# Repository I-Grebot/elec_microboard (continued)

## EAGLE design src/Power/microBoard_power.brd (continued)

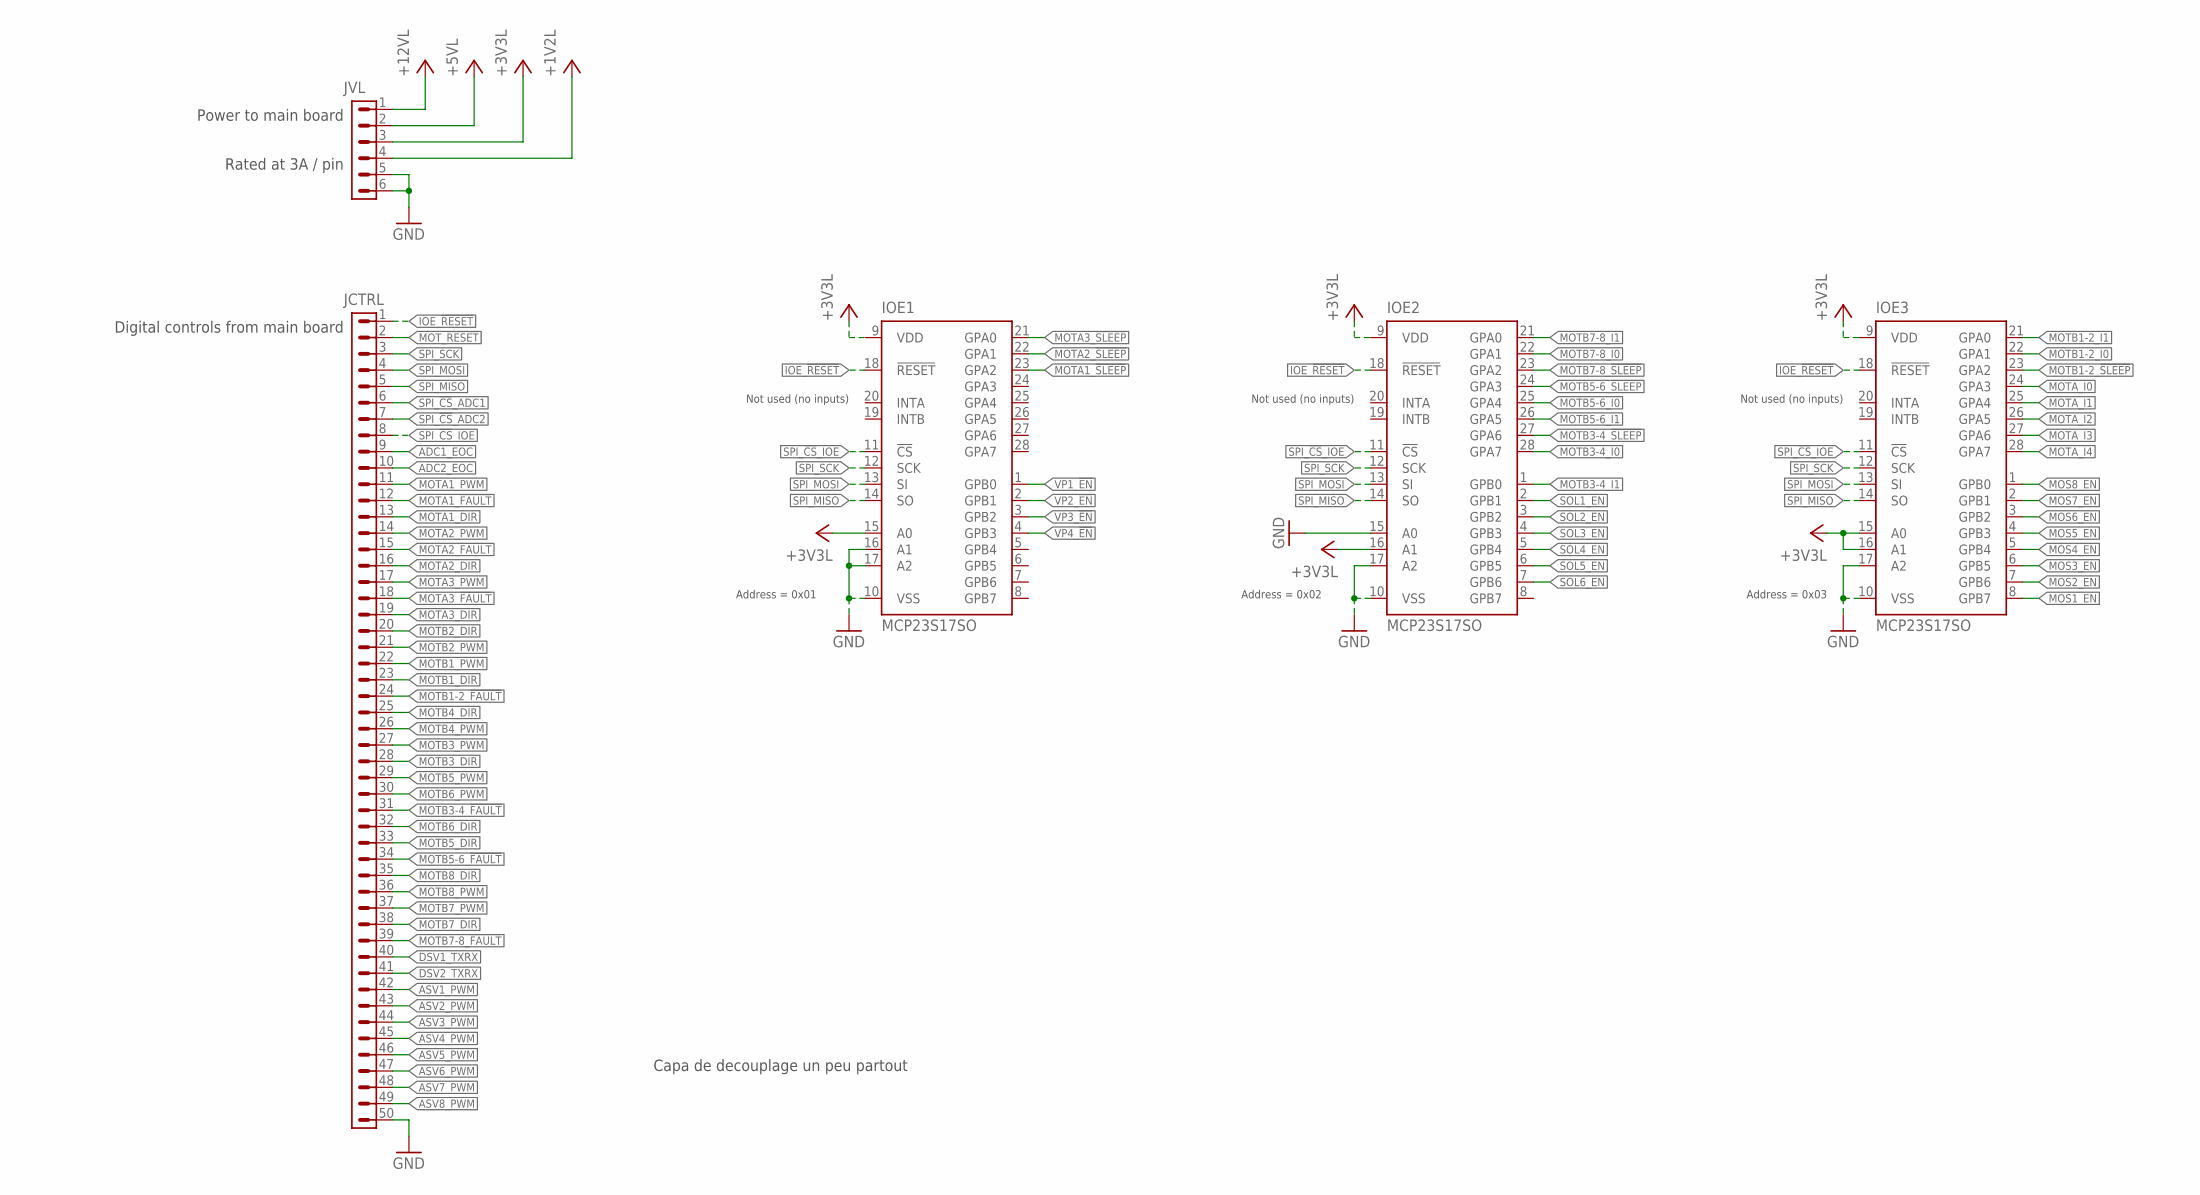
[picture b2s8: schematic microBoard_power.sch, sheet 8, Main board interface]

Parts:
IOE1, IOE2, IOE3: MCP23S17SO; SO28W
JCTRL: FFC-0.5_50; FFC-SMD-0.5_50
JVL: HE14_H_6

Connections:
+1V2L: JVL.4; also elsewhere on the board
+3V3L: IOE1.9 (VDD), IOE1.15 (A0), IOE2.9 (VDD), IOE2.16 (A1), IOE3.9 (VDD), IOE3.15 (A0), IOE3.16 (A1), JVL.3; also elsewhere on the board
+5VL: JVL.2; also elsewhere on the board
+12VL: JVL.1; also elsewhere on the board
ADC1_EOC: JCTRL.9; also elsewhere on the board
ADC2_EOC: JCTRL.10; also elsewhere on the board
ASV1_PWM: JCTRL.42; also elsewhere on the board
ASV2_PWM: JCTRL.43; also elsewhere on the board
ASV3_PWM: JCTRL.44; also elsewhere on the board
ASV4_PWM: JCTRL.45; also elsewhere on the board
ASV5_PWM: JCTRL.46; also elsewhere on the board
ASV6_PWM: JCTRL.47; also elsewhere on the board
ASV7_PWM: JCTRL.48; also elsewhere on the board
ASV8_PWM: JCTRL.49; also elsewhere on the board
DSV1_TXRX: JCTRL.40; also elsewhere on the board
DSV2_TXRX: JCTRL.41
GND: IOE1.10 (VSS), IOE1.16 (A1), IOE1.17 (A2), IOE2.10 (VSS), IOE2.15 (A0), IOE2.17 (A2), IOE3.10 (VSS), IOE3.17 (A2), JCTRL.50, JVL.5, JVL.6; also elsewhere on the board
IOE_!RESET!: IOE1.18 (!RESET), IOE2.18 (!RESET), IOE3.18 (!RESET), JCTRL.1
MOS1_EN: IOE3.8 (GPB7); also elsewhere on the board
MOS2_EN: IOE3.7 (GPB6); also elsewhere on the board
MOS3_EN: IOE3.6 (GPB5); also elsewhere on the board
MOS4_EN: IOE3.5 (GPB4); also elsewhere on the board
MOS5_EN: IOE3.4 (GPB3); also elsewhere on the board
MOS6_EN: IOE3.3 (GPB2); also elsewhere on the board
MOS7_EN: IOE3.2 (GPB1); also elsewhere on the board
MOS8_EN: IOE3.1 (GPB0); also elsewhere on the board
MOTA1_!FAULT!: JCTRL.12; also elsewhere on the board
MOTA1_!SLEEP!: IOE1.23 (GPA2); also elsewhere on the board
MOTA1_DIR: JCTRL.13; also elsewhere on the board
MOTA1_PWM: JCTRL.11; also elsewhere on the board
MOTA2_!FAULT!: JCTRL.15; also elsewhere on the board
MOTA2_!SLEEP!: IOE1.22 (GPA1); also elsewhere on the board
MOTA2_DIR: JCTRL.16; also elsewhere on the board
MOTA2_PWM: JCTRL.14; also elsewhere on the board
MOTA3_!FAULT!: JCTRL.18; also elsewhere on the board
MOTA3_!SLEEP!: IOE1.21 (GPA0); also elsewhere on the board
MOTA3_DIR: JCTRL.19; also elsewhere on the board
MOTA3_PWM: JCTRL.17; also elsewhere on the board
MOTA_I0: IOE3.24 (GPA3); also elsewhere on the board
MOTA_I1: IOE3.25 (GPA4); also elsewhere on the board
MOTA_I2: IOE3.26 (GPA5); also elsewhere on the board
MOTA_I3: IOE3.27 (GPA6); also elsewhere on the board
MOTA_I4: IOE3.28 (GPA7); also elsewhere on the board
MOTB1-2_!FAULT!: JCTRL.24; also elsewhere on the board
MOTB1-2_!SLEEP!: IOE3.23 (GPA2); also elsewhere on the board
MOTB1-2_I0: IOE3.22 (GPA1); also elsewhere on the board
MOTB1-2_I1: IOE3.21 (GPA0); also elsewhere on the board
MOTB1_DIR: JCTRL.23; also elsewhere on the board
MOTB1_PWM: JCTRL.22; also elsewhere on the board
MOTB2_DIR: JCTRL.20; also elsewhere on the board
MOTB2_PWM: JCTRL.21; also elsewhere on the board
MOTB3-4_!FAULT!: JCTRL.31; also elsewhere on the board
MOTB3-4_!SLEEP!: IOE2.27 (GPA6); also elsewhere on the board
MOTB3-4_I0: IOE2.28 (GPA7); also elsewhere on the board
MOTB3-4_I1: IOE2.1 (GPB0); also elsewhere on the board
MOTB3_DIR: JCTRL.28; also elsewhere on the board
MOTB3_PWM: JCTRL.27; also elsewhere on the board
MOTB4_DIR: JCTRL.25; also elsewhere on the board
MOTB4_PWM: JCTRL.26; also elsewhere on the board
MOTB5-6_!FAULT!: JCTRL.34; also elsewhere on the board
MOTB5-6_!SLEEP!: IOE2.24 (GPA3); also elsewhere on the board
MOTB5-6_I0: IOE2.25 (GPA4); also elsewhere on the board
MOTB5-6_I1: IOE2.26 (GPA5); also elsewhere on the board
MOTB5_DIR: JCTRL.33; also elsewhere on the board
MOTB5_PWM: JCTRL.29; also elsewhere on the board
MOTB6_DIR: JCTRL.32; also elsewhere on the board
MOTB6_PWM: JCTRL.30; also elsewhere on the board
MOTB7-8_!FAULT!: JCTRL.39; also elsewhere on the board
MOTB7-8_!SLEEP!: IOE2.23 (GPA2); also elsewhere on the board
MOTB7-8_I0: IOE2.22 (GPA1); also elsewhere on the board
MOTB7-8_I1: IOE2.21 (GPA0); also elsewhere on the board
MOTB7_DIR: JCTRL.38; also elsewhere on the board
MOTB7_PWM: JCTRL.37; also elsewhere on the board
MOTB8_DIR: JCTRL.35; also elsewhere on the board
MOTB8_PWM: JCTRL.36; also elsewhere on the board
MOT_!RESET!: JCTRL.2; also elsewhere on the board
SOL1_EN: IOE2.2 (GPB1); also elsewhere on the board
SOL2_EN: IOE2.3 (GPB2); also elsewhere on the board
SOL3_EN: IOE2.4 (GPB3); also elsewhere on the board
SOL4_EN: IOE2.5 (GPB4); also elsewhere on the board
SOL5_EN: IOE2.6 (GPB5); also elsewhere on the board
SOL6_EN: IOE2.7 (GPB6); also elsewhere on the board
SPI_!CS!_ADC1: JCTRL.6; also elsewhere on the board
SPI_!CS!_ADC2: JCTRL.7; also elsewhere on the board
SPI_!CS!_IOE: IOE1.11 (!CS), IOE2.11 (!CS), IOE3.11 (!CS), JCTRL.8
SPI_MISO: IOE1.14 (SO), IOE2.14 (SO), IOE3.14 (SO), JCTRL.5; also elsewhere on the board
SPI_MOSI: IOE1.13 (SI), IOE2.13 (SI), IOE3.13 (SI), JCTRL.4; also elsewhere on the board
SPI_SCK: IOE1.12 (SCK), IOE2.12 (SCK), IOE3.12 (SCK), JCTRL.3; also elsewhere on the board
VP1_!EN!: IOE1.1 (GPB0); also elsewhere on the board
VP2_!EN!: IOE1.2 (GPB1); also elsewhere on the board
VP3_!EN!: IOE1.3 (GPB2); also elsewhere on the board
VP4_!EN!: IOE1.4 (GPB3); also elsewhere on the board

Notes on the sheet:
Not used (no inputs)
Power to main board
Rated at 3A / pin
Digital controls from main board
Address = 0x01
Address = 0x02
Address = 0x03
Capa de decouplage un peu partout

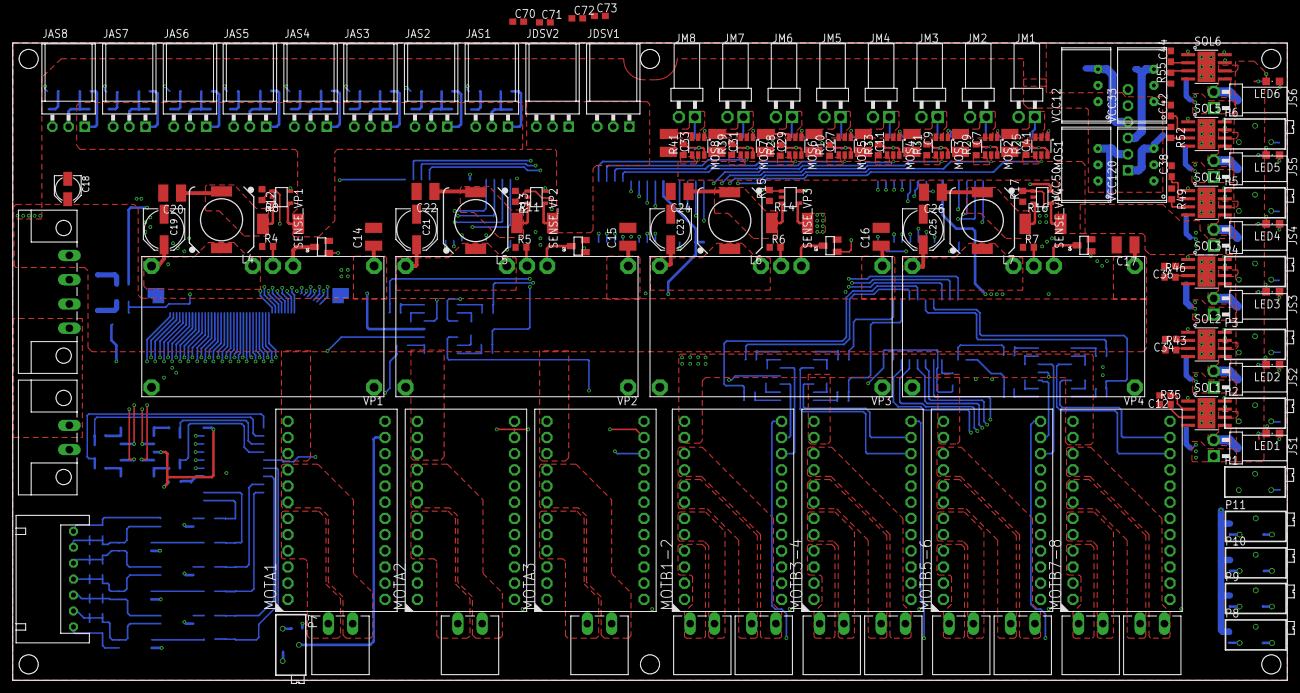
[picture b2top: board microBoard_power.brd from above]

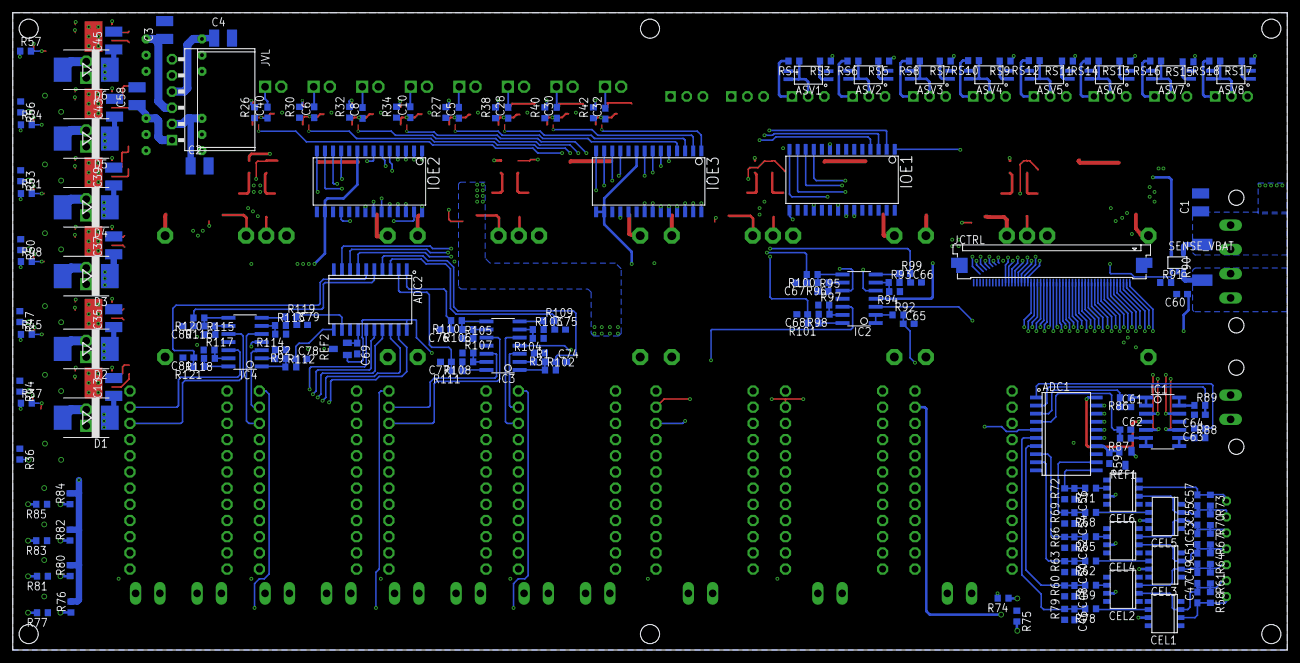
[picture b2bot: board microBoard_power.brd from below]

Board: 4 copper layers, 200.0 x 100.0 mm, 341 parts (188 on the bottom side), 314 nets.

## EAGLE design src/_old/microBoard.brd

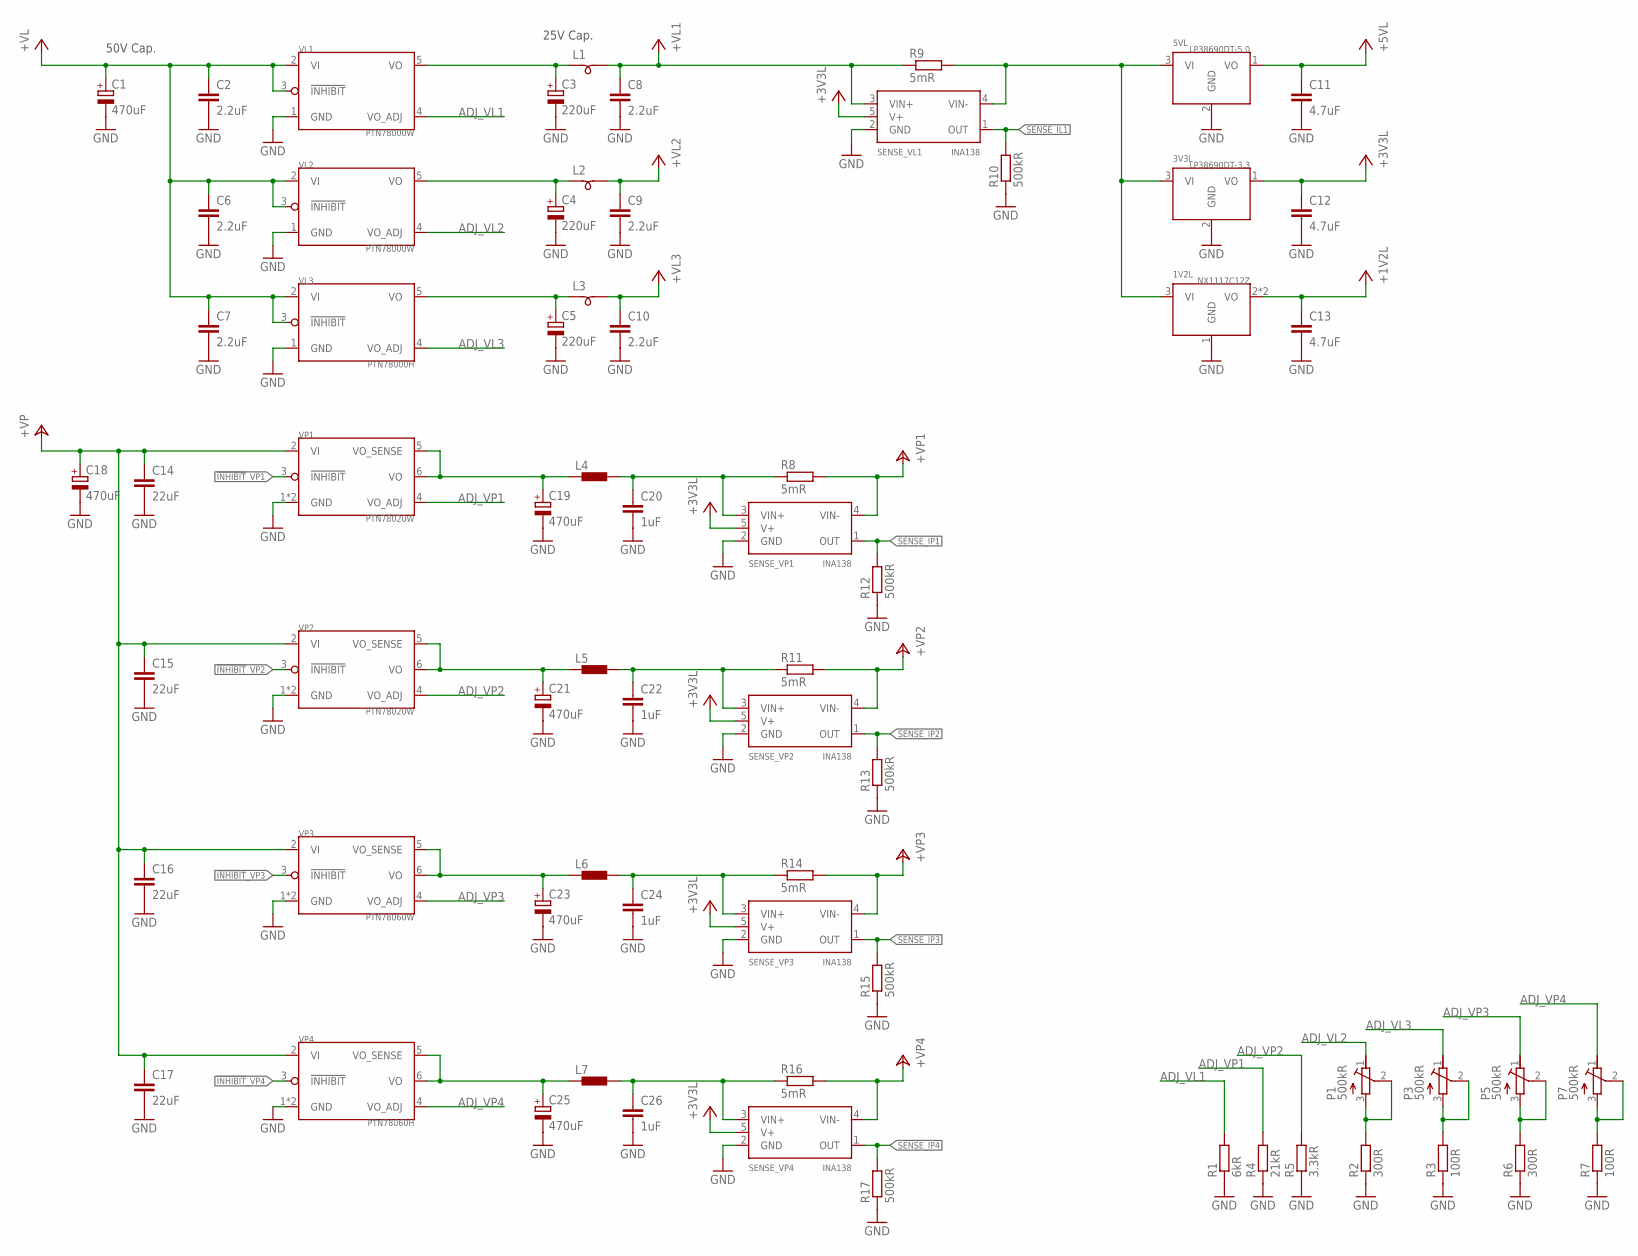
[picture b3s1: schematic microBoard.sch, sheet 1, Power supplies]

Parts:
1V2L: NX1117C12Z; SOT_223
3V3L: LP38690DT-3.3; NDP_0003B
5VL: LP38690DT-5.0; NDP_0003B
C1, C18: 470uF; PANASONIC_B
C2, C6, C7, C8, C9, C10: 2.2uF; C3225
C3, C4, C5: 220uF; PANASONIC_B
C11, C12, C13: 4.7uF; C3225
C14, C15, C16, C17: 22uF; C3225
C19, C21, C23, C25: 470uF; PANASONIC_D
C20, C22, C24, C26: 1uF; C3225
L1, L2, L3: SM-B9
L4, L5, L6, L7: DR1030
P1, P3, P5, P7: 500kR; RTRIMT93XB
R1: 6kR; R0603
R2, R6: 300R; R0603
R3, R7: 100R; R0603
R4: 21kR; R0603
R5: 3.3kR; R0603
R8, R9, R11, R14, R16: 5mR; R2512
R10, R12, R13, R15, R17: 500kR; R0603
SENSE_VL1: INA138; DBV_05
SENSE_VP1, SENSE_VP2, SENSE_VP3, SENSE_VP4: INA138; DBV_05
VL1, VL2: PTN78000W; PTN78000
VL3: PTN78000H; PTN78000
VP1, VP2: PTN78020W; PTN78020
VP3: PTN78060W; PTN78060
VP4: PTN78060H; PTN78060

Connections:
!INHIBIT!_VP1: VP1.3 (!INHIBIT!)
!INHIBIT!_VP2: VP2.3 (!INHIBIT!)
!INHIBIT!_VP3: VP3.3 (!INHIBIT!)
!INHIBIT!_VP4: VP4.3 (!INHIBIT!)
+1V2L: 1V2L.2 (VO), 1V2L.4 (VO), C13.1; also elsewhere on the board
+3V3L: 3V3L.1 (VO), C12.1, SENSE_VL1.5 (V+), SENSE_VP1.5 (V+), SENSE_VP2.5 (V+), SENSE_VP3.5 (V+), SENSE_VP4.5 (V+); also elsewhere on the board
+5VL: 5VL.1 (VO), C11.1; also elsewhere on the board
+VL: C1.+, C2.1, C6.1, C7.1, VL1.2 (VI), VL1.3 (!INHIBIT!), VL2.2 (VI), VL2.3 (!INHIBIT!), VL3.2 (VI), VL3.3 (!INHIBIT!)
+VL1: C8.1, L1.2, R9.1, SENSE_VL1.3 (VIN+)
+VL2: C9.1, L2.2; also elsewhere on the board
+VL3: C10.1, L3.2
+VP: C14.1, C15.1, C16.1, C17.1, C18.+, VP1.2 (VI), VP2.2 (VI), VP3.2 (VI), VP4.2 (VI); also elsewhere on the board
+VP1: R8.2, SENSE_VP1.4 (VIN-); also elsewhere on the board
+VP2: R11.2, SENSE_VP2.4 (VIN-)
+VP3: R14.2, SENSE_VP3.4 (VIN-); also elsewhere on the board
+VP4: R16.2, SENSE_VP4.4 (VIN-); also elsewhere on the board
ADJ_VL1: R1.2, VL1.4 (VO_ADJ)
ADJ_VL2: P1.1 (A), VL2.4 (VO_ADJ)
ADJ_VL3: P3.1 (A), VL3.4 (VO_ADJ)
ADJ_VP1: R4.2, VP1.4 (VO_ADJ)
ADJ_VP2: R5.2, VP2.4 (VO_ADJ)
ADJ_VP3: P5.1 (A), VP3.4 (VO_ADJ)
ADJ_VP4: P7.1 (A), VP4.4 (VO_ADJ)
GND: 1V2L.1 (GND), 3V3L.2 (GND), 5VL.2 (GND), C1.-, C2.2, C3.-, C4.-, C5.-, C6.2, C7.2, C8.2, C9.2, C10.2, C11.2, C12.2, C13.2, C14.2, C15.2, C16.2, C17.2, C18.-, C19.-, C20.2, C21.-, C22.2, C23.-, C24.2, C25.-, C26.2, R1.1, R2.1, R3.1, R4.1, R5.1, R6.1, R7.1, R10.1, R12.1, R13.1, R15.1, R17.1, SENSE_VL1.2 (GND), SENSE_VP1.2 (GND), SENSE_VP2.2 (GND), SENSE_VP3.2 (GND), SENSE_VP4.2 (GND), VL1.1 (GND), VL2.1 (GND), VL3.1 (GND), VP1.1 (GND), VP1.7 (GND), VP2.1 (GND), VP2.7 (GND), VP3.1 (GND), VP3.7 (GND), VP4.1 (GND), VP4.7 (GND); also elsewhere on the board
unnamed: C19.+, L4.1, VP1.5 (VO_SENSE), VP1.6 (VO)
unnamed: P1.2 (S), P1.3 (E), R2.2
unnamed: C20.1, L4.2, R8.1, SENSE_VP1.3 (VIN+)
unnamed: P3.2 (S), P3.3 (E), R3.2
unnamed: P5.2 (S), P5.3 (E), R6.2
unnamed: C21.+, L5.1, VP2.5 (VO_SENSE), VP2.6 (VO)
unnamed: C3.+, L1.1, VL1.5 (VO)
unnamed: C4.+, L2.1, VL2.5 (VO)
unnamed: C5.+, L3.1, VL3.5 (VO)
unnamed: P7.2 (S), P7.3 (E), R7.2
unnamed: C22.1, L5.2, R11.1, SENSE_VP2.3 (VIN+)
unnamed: C23.+, L6.1, VP3.5 (VO_SENSE), VP3.6 (VO)
unnamed: C24.1, L6.2, R14.1, SENSE_VP3.3 (VIN+)
unnamed: C25.+, L7.1, VP4.5 (VO_SENSE), VP4.6 (VO)
unnamed: C26.1, L7.2, R16.1, SENSE_VP4.3 (VIN+)
SENSE_IL1: R10.2, SENSE_VL1.1 (OUT); also elsewhere on the board
SENSE_IP1: R12.2, SENSE_VP1.1 (OUT); also elsewhere on the board
SENSE_IP2: R13.2, SENSE_VP2.1 (OUT); also elsewhere on the board
SENSE_IP3: R15.2, SENSE_VP3.1 (OUT); also elsewhere on the board
SENSE_IP4: R17.2, SENSE_VP4.1 (OUT); also elsewhere on the board
VS1: 1V2L.3 (VI), 3V3L.3 (VI), 5VL.3 (VI), R9.2, SENSE_VL1.4 (VIN-)

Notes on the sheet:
50V Cap.
25V Cap.

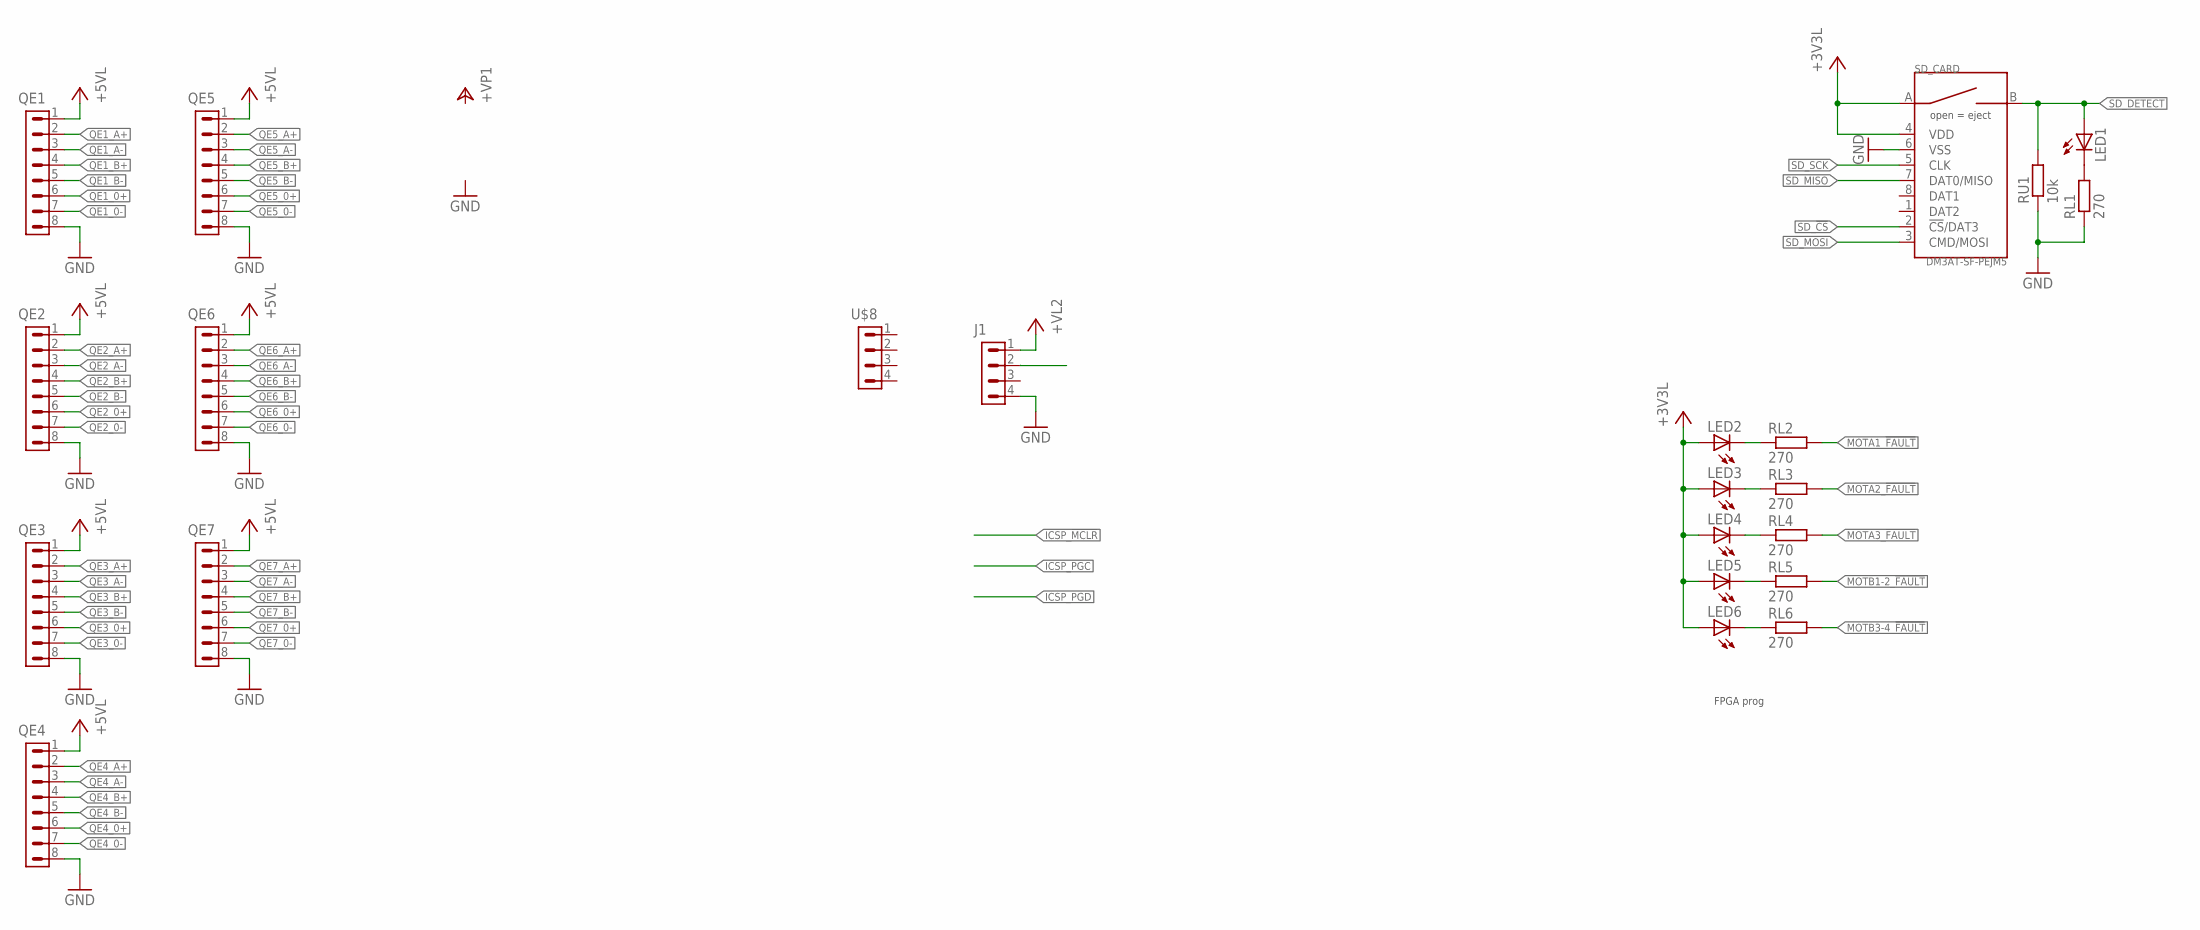
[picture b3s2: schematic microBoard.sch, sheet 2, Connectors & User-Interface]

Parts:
J1: CON_1.27_4
LED1, LED2, LED3, LED4, LED5, LED6: LEDCHIP-LED0805; CHIP-LED0805
QE1, QE2, QE3, QE4, QE5, QE6, QE7: CON_1.27_8
RL1, RL2, RL3, RL4, RL5, RL6: 270; R0603
RU1: 10k; R0603
SD_CARD: DM3AT-SF-PEJM5; DM3AT
U$8: CON_1.25_4

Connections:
+3V3L: LED2.A, LED3.A, LED4.A, LED5.A, LED6.A, SD_CARD.4 (VDD), SD_CARD.A; also elsewhere on the board
+5VL: QE1.1, QE2.1, QE3.1, QE4.1, QE5.1, QE6.1, QE7.1; also elsewhere on the board
+VL2: J1.1; also elsewhere on the board
GND: J1.4, QE1.8, QE2.8, QE3.8, QE4.8, QE5.8, QE6.8, QE7.8, RL1.1, RU1.1, SD_CARD.6 (VSS); also elsewhere on the board
MOTA1_!FAULT!: RL2.2; also elsewhere on the board
MOTA2_!FAULT!: RL3.2; also elsewhere on the board
MOTA3_!FAULT!: RL4.2; also elsewhere on the board
MOTB1-2_!FAULT!: RL5.2; also elsewhere on the board
MOTB3-4_!FAULT!: RL6.2; also elsewhere on the board
unnamed: LED1.C, RL1.2
unnamed: LED2.C, RL2.1
unnamed: LED3.C, RL3.1
unnamed: LED4.C, RL4.1
unnamed: LED5.C, RL5.1
unnamed: LED6.C, RL6.1
QE1_0+: QE1.6; also elsewhere on the board
QE1_0-: QE1.7; also elsewhere on the board
QE1_A+: QE1.2; also elsewhere on the board
QE1_A-: QE1.3; also elsewhere on the board
QE1_B+: QE1.4; also elsewhere on the board
QE1_B-: QE1.5; also elsewhere on the board
QE2_0+: QE2.6; also elsewhere on the board
QE2_0-: QE2.7; also elsewhere on the board
QE2_A+: QE2.2; also elsewhere on the board
QE2_A-: QE2.3; also elsewhere on the board
QE2_B+: QE2.4; also elsewhere on the board
QE2_B-: QE2.5; also elsewhere on the board
QE3_0+: QE3.6; also elsewhere on the board
QE3_0-: QE3.7; also elsewhere on the board
QE3_A+: QE3.2; also elsewhere on the board
QE3_A-: QE3.3; also elsewhere on the board
QE3_B+: QE3.4; also elsewhere on the board
QE3_B-: QE3.5; also elsewhere on the board
QE4_0+: QE4.6; also elsewhere on the board
QE4_0-: QE4.7; also elsewhere on the board
QE4_A+: QE4.2; also elsewhere on the board
QE4_A-: QE4.3; also elsewhere on the board
QE4_B+: QE4.4; also elsewhere on the board
QE4_B-: QE4.5; also elsewhere on the board
QE5_0+: QE5.6; also elsewhere on the board
QE5_0-: QE5.7; also elsewhere on the board
QE5_A+: QE5.2; also elsewhere on the board
QE5_A-: QE5.3; also elsewhere on the board
QE5_B+: QE5.4; also elsewhere on the board
QE5_B-: QE5.5; also elsewhere on the board
QE6_0+: QE6.6; also elsewhere on the board
QE6_0-: QE6.7; also elsewhere on the board
QE6_A+: QE6.2; also elsewhere on the board
QE6_A-: QE6.3; also elsewhere on the board
QE6_B+: QE6.4; also elsewhere on the board
QE6_B-: QE6.5; also elsewhere on the board
QE7_0+: QE7.6; also elsewhere on the board
QE7_0-: QE7.7; also elsewhere on the board
QE7_A+: QE7.2; also elsewhere on the board
QE7_A-: QE7.3; also elsewhere on the board
QE7_B+: QE7.4; also elsewhere on the board
QE7_B-: QE7.5; also elsewhere on the board
SD_!CS!: SD_CARD.2 (!CS!/DAT3); also elsewhere on the board
SD_DETECT: LED1.A, RU1.2, SD_CARD.B
SD_MISO: SD_CARD.7 (DAT0/MISO); also elsewhere on the board
SD_MOSI: SD_CARD.3 (CMD/MOSI); also elsewhere on the board
SD_SCK: SD_CARD.5 (CLK); also elsewhere on the board

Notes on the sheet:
FPGA prog

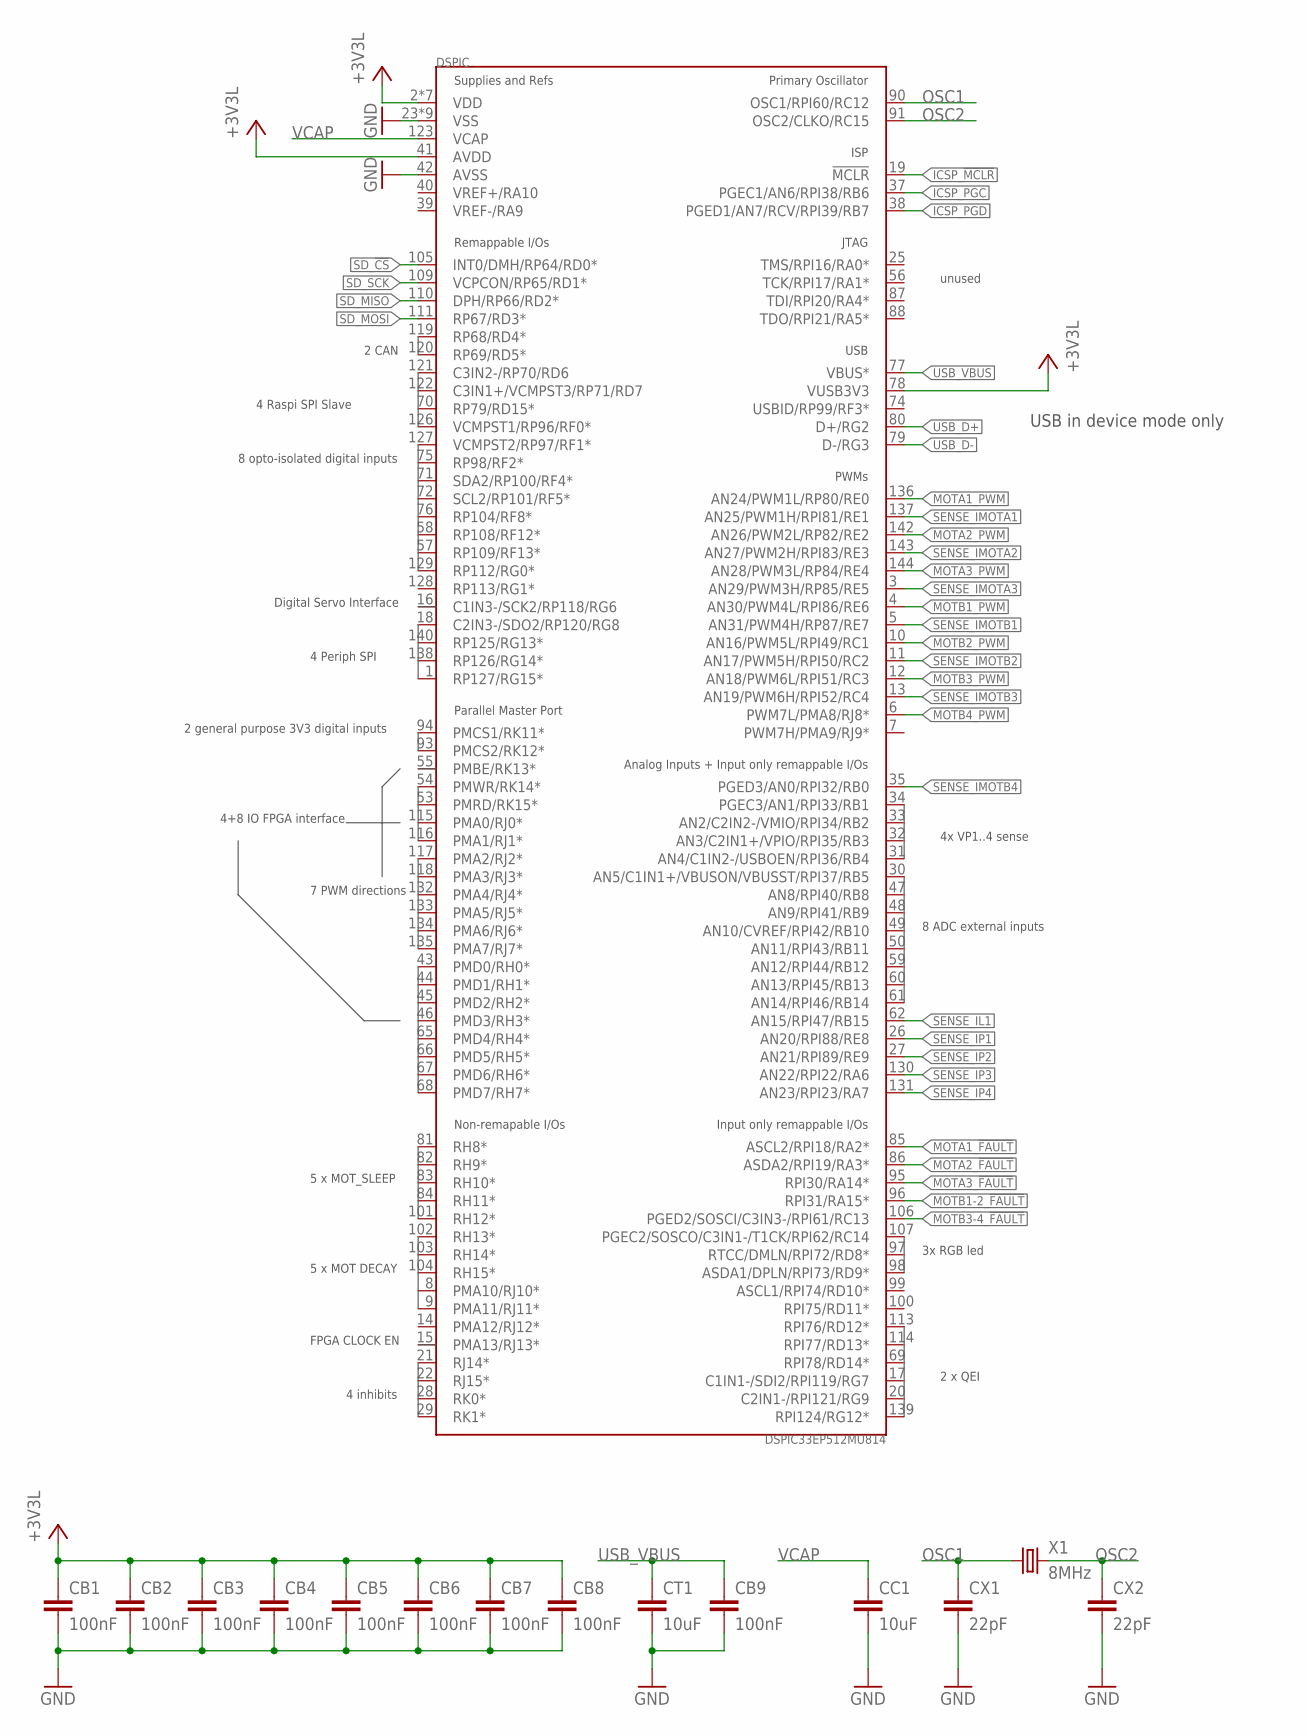
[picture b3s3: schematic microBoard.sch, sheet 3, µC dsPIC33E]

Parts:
CB1, CB2, CB3, CB4, CB5, CB6, CB7, CB8, CB9: 100nF; C0603
CC1: 10uF; C1210
CT1: 10uF; C1210
CX1, CX2: 22pF; C0603
DSPIC: DSPIC33EP512MU814; TQFP_144
X1: 8MHz; CTS406

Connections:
+3V3L: CB1.1, CB2.1, CB3.1, CB4.1, CB5.1, CB6.1, CB7.1, CB8.1, DSPIC.2 (VDD), DSPIC.24 (VDD), DSPIC.41 (AVDD), DSPIC.52 (VDD), DSPIC.64 (VDD), DSPIC.78 (VUSB3V3), DSPIC.89 (VDD), DSPIC.112 (VDD), DSPIC.124 (VDD); also elsewhere on the board
GND: CB1.2, CB2.2, CB3.2, CB4.2, CB5.2, CB6.2, CB7.2, CB8.2, CB9.2, CC1.2, CT1.2, CX1.2, CX2.2, DSPIC.23 (VSS), DSPIC.36 (VSS), DSPIC.42 (AVSS), DSPIC.51 (VSS), DSPIC.63 (VSS), DSPIC.73 (VSS), DSPIC.92 (VSS), DSPIC.108 (VSS), DSPIC.125 (VSS), DSPIC.141 (VSS); also elsewhere on the board
ICSP_!MCLR!: DSPIC.19 (!MCLR!)
ICSP_PGC: DSPIC.37 (PGEC1/AN6/RPI38/RB6)
ICSP_PGD: DSPIC.38 (PGED1/AN7/RCV/RPI39/RB7)
MOTA1_!FAULT!: DSPIC.85 (ASCL2/RPI18/RA2*); also elsewhere on the board
MOTA1_PWM: DSPIC.136 (AN24/PWM1L/RP80/RE0); also elsewhere on the board
MOTA2_!FAULT!: DSPIC.86 (ASDA2/RPI19/RA3*); also elsewhere on the board
MOTA2_PWM: DSPIC.142 (AN26/PWM2L/RP82/RE2); also elsewhere on the board
MOTA3_!FAULT!: DSPIC.95 (RPI30/RA14*); also elsewhere on the board
MOTA3_PWM: DSPIC.144 (AN28/PWM3L/RP84/RE4); also elsewhere on the board
MOTB1-2_!FAULT!: DSPIC.96 (RPI31/RA15*); also elsewhere on the board
MOTB1_PWM: DSPIC.4 (AN30/PWM4L/RPI86/RE6); also elsewhere on the board
MOTB2_PWM: DSPIC.10 (AN16/PWM5L/RPI49/RC1); also elsewhere on the board
MOTB3-4_!FAULT!: DSPIC.106 (PGED2/SOSCI/C3IN3-/RPI61/RC13); also elsewhere on the board
MOTB3_PWM: DSPIC.12 (AN18/PWM6L/RPI51/RC3); also elsewhere on the board
MOTB4_PWM: DSPIC.6 (PWM7L/PMA8/RJ8*); also elsewhere on the board
OSC1: CX1.1, DSPIC.90 (OSC1/RPI60/RC12), X1.1
OSC2: CX2.1, DSPIC.91 (OSC2/CLKO/RC15), X1.3 (2)
SD_!CS!: DSPIC.105 (INT0/DMH/RP64/RD0*); also elsewhere on the board
SD_MISO: DSPIC.110 (DPH/RP66/RD2*); also elsewhere on the board
SD_MOSI: DSPIC.111 (RP67/RD3*); also elsewhere on the board
SD_SCK: DSPIC.109 (VCPCON/RP65/RD1*); also elsewhere on the board
SENSE_IL1: DSPIC.62 (AN15/RPI47/RB15); also elsewhere on the board
SENSE_IMOTA1: DSPIC.137 (AN25/PWM1H/RPI81/RE1); also elsewhere on the board
SENSE_IMOTA2: DSPIC.143 (AN27/PWM2H/RPI83/RE3); also elsewhere on the board
SENSE_IMOTA3: DSPIC.3 (AN29/PWM3H/RP85/RE5); also elsewhere on the board
SENSE_IMOTB1: DSPIC.5 (AN31/PWM4H/RP87/RE7); also elsewhere on the board
SENSE_IMOTB2: DSPIC.11 (AN17/PWM5H/RPI50/RC2); also elsewhere on the board
SENSE_IMOTB3: DSPIC.13 (AN19/PWM6H/RPI52/RC4); also elsewhere on the board
SENSE_IMOTB4: DSPIC.35 (PGED3/AN0/RPI32/RB0); also elsewhere on the board
SENSE_IP1: DSPIC.26 (AN20/RPI88/RE8); also elsewhere on the board
SENSE_IP2: DSPIC.27 (AN21/RPI89/RE9); also elsewhere on the board
SENSE_IP3: DSPIC.130 (AN22/RPI22/RA6); also elsewhere on the board
SENSE_IP4: DSPIC.131 (AN23/RPI23/RA7); also elsewhere on the board
USB_D+: DSPIC.80 (D+/RG2)
USB_D-: DSPIC.79 (D-/RG3)
USB_VBUS: CB9.1, CT1.1, DSPIC.77 (VBUS*)
VCAP: CC1.1, DSPIC.123 (VCAP)

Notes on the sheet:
USB in device mode only
unused
2 x QEI
4 inhibits
4+8 IO FPGA interface
FPGA CLOCK EN
8 opto-isolated digital inputs
2 general purpose 3V3 digital inputs
Digital Servo Interface
2 CAN
4 Raspi SPI Slave
4 Periph SPI
7 PWM directions
8 ADC external inputs
4x VP1..4 sense
3x RGB led
5 x MOT_SLEEP
5 x MOT DECAY

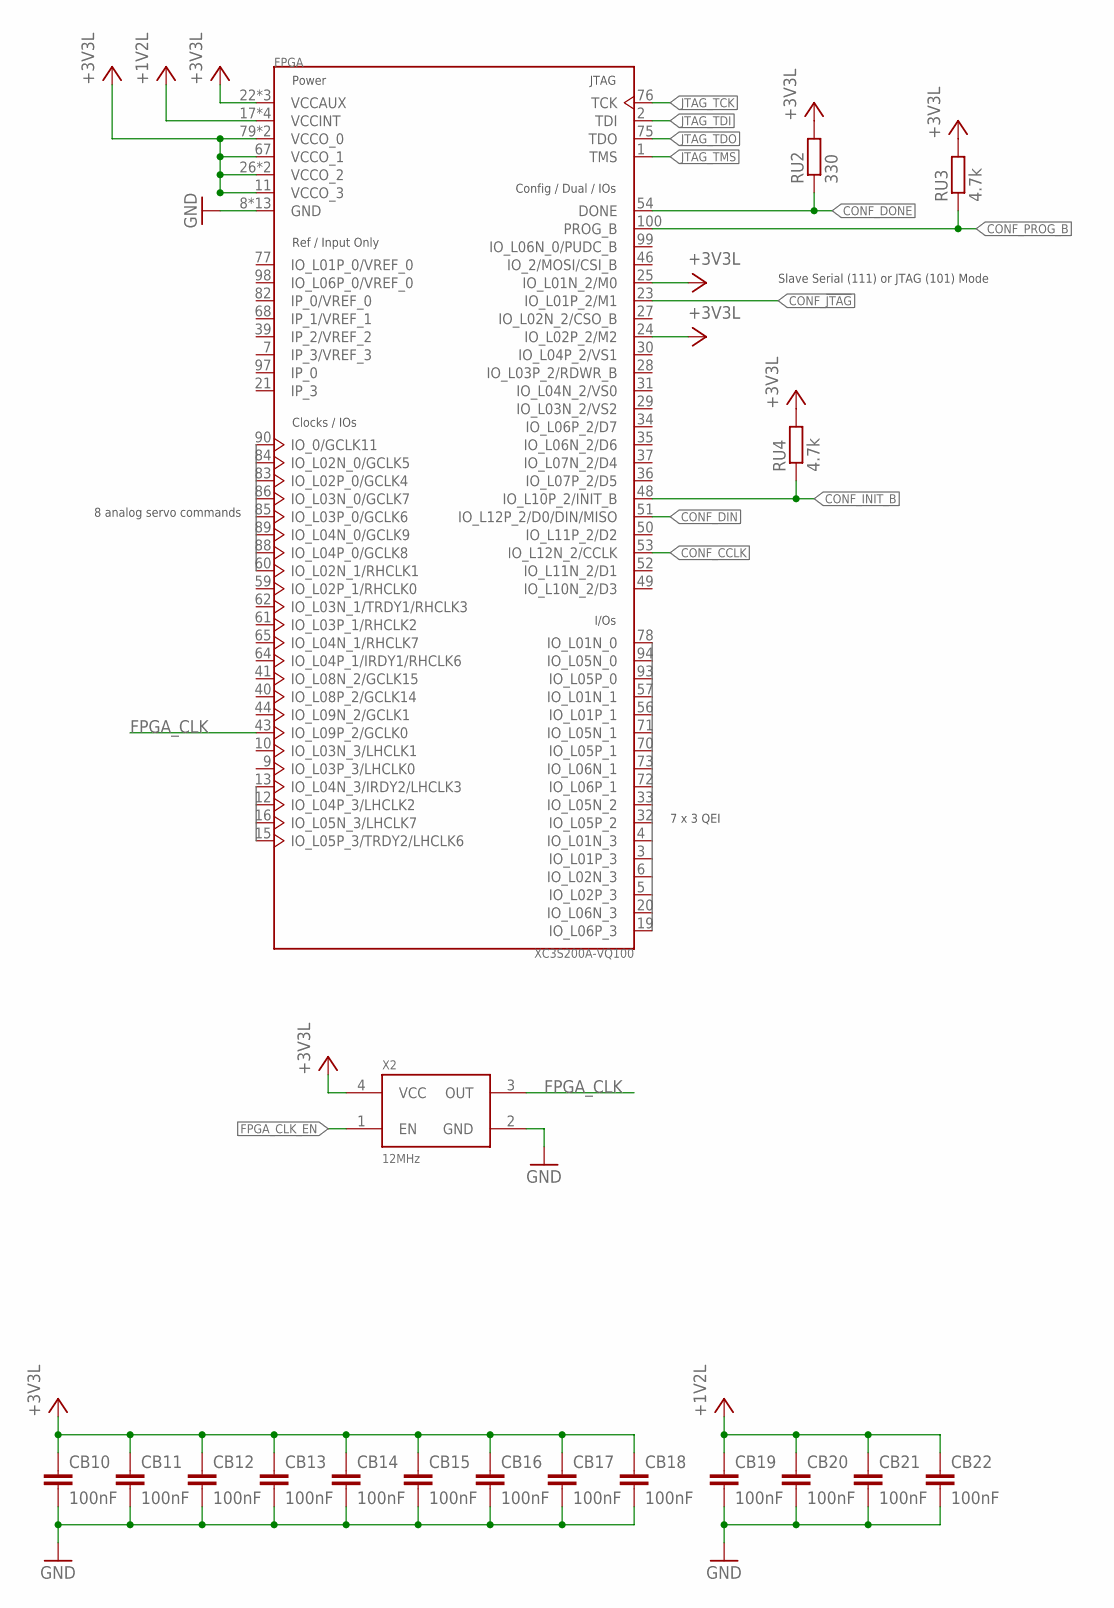
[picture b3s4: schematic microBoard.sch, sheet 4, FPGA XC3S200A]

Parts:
CB10, CB11, CB12, CB13, CB14, CB15, CB16, CB17, CB18, CB19, CB20, CB21, CB22: 100nF; C0603
FPGA: XC3S200A-VQ100; VQFP_100
RU2: 330; R0603
RU3, RU4: 4.7k; R0603
X2: 12MHz; CRYSTAL-SMD-5X3

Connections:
+1V2L: CB19.1, CB20.1, CB21.1, CB22.1, FPGA.17 (VCCINT), FPGA.38 (VCCINT), FPGA.66 (VCCINT), FPGA.81 (VCCINT); also elsewhere on the board
+3V3L: CB10.1, CB11.1, CB12.1, CB13.1, CB14.1, CB15.1, CB16.1, CB17.1, CB18.1, FPGA.11 (VCCO_3), FPGA.22 (VCCAUX), FPGA.24 (IO_L02P_2/M2), FPGA.25 (IO_L01N_2/M0), FPGA.26 (VCCO_2), FPGA.45 (VCCO_2), FPGA.55 (VCCAUX), FPGA.67 (VCCO_1), FPGA.79 (VCCO_0), FPGA.92 (VCCAUX), FPGA.96 (VCCO_0), RU2.2, RU3.2, RU4.2, X2.4 (VCC); also elsewhere on the board
CONF_!JTAG!: FPGA.23 (IO_L01P_2/M1)
CONF_CCLK: FPGA.53 (IO_L12N_2/CCLK)
CONF_DIN: FPGA.51 (IO_L12P_2/D0/DIN/MISO)
CONF_DONE: FPGA.54 (DONE), RU2.1
CONF_INIT_B: FPGA.48 (IO_L10P_2/INIT_B), RU4.1
CONF_PROG_B: FPGA.100 (PROG_B), RU3.1
FPGA_CLK: FPGA.43 (IO_L09P_2/GCLK0), X2.3 (OUT)
FPGA_CLK_EN: X2.1 (EN)
GND: CB10.2, CB11.2, CB12.2, CB13.2, CB14.2, CB15.2, CB16.2, CB17.2, CB18.2, CB19.2, CB20.2, CB21.2, CB22.2, FPGA.8 (GND), FPGA.14 (GND), FPGA.18 (GND), FPGA.42 (GND), FPGA.47 (GND), FPGA.58 (GND), FPGA.63 (GND), FPGA.69 (GND), FPGA.74 (GND), FPGA.80 (GND), FPGA.87 (GND), FPGA.91 (GND), FPGA.95 (GND), X2.2 (GND); also elsewhere on the board
JTAG_TCK: FPGA.76 (TCK)
JTAG_TDI: FPGA.2 (TDI)
JTAG_TDO: FPGA.75 (TDO)
JTAG_TMS: FPGA.1 (TMS)

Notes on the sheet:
7 x 3 QEI
Slave Serial (111) or JTAG (101) Mode
8 analog servo commands
